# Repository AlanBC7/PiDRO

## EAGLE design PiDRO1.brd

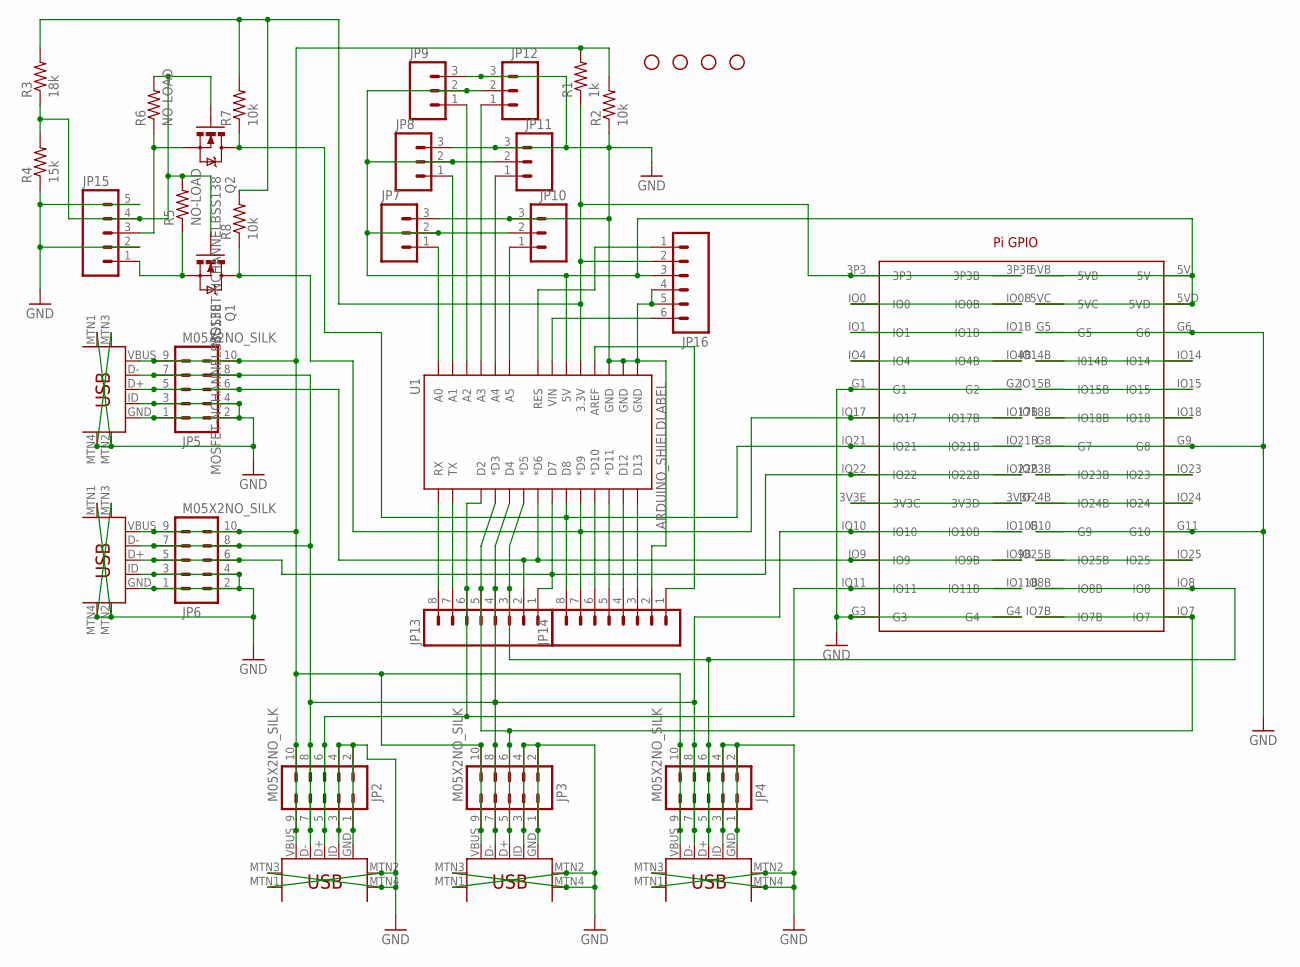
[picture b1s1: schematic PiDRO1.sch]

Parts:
JP2, JP3, JP4, JP5, JP6: M05X2NO_SILK; 2X5_NOSILK
JP7, JP8, JP9, JP10, JP11, JP12: M03LOCK_NO_SILK; 1X03_LOCK_NO_SILK
JP13, JP14: M08; 1X08_PIN1_NO_SILK
JP15: M05PTH; 1X05
JP16: M06LOCK; 1X06_LOCK
Q1, Q2: MOSFET-NCHANNELBSS138; SOT23
R1: 1k; 0805
R2, R7, R8: 10k; 0805
R3: 18k; 0805
R4: 15k; 0805
R5, R6: NO-LOAD; 0805
STANDOFF1, STANDOFF2, STANDOFF3, STANDOFF4: STAND-OFF
U1: ARDUINO_SHIELDLABEL; DUEMILANOVE_SHIELD
U$1: PIGPIO_2X; PI_GPIO_2X
U$2, U$3, U$4, U$5, U$6: USB-MINIB-5PIN; USB-MINIB

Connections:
GND: JP2.1, JP2.2, JP2.3, JP2.4, JP3.1, JP3.2, JP3.3, JP3.4, JP4.1, JP4.2, JP4.3, JP4.4, JP5.1, JP5.2, JP5.3, JP5.4, JP6.1, JP6.2, JP6.3, JP6.4, JP7.3, JP8.3, JP9.3, JP10.3, JP11.3, JP12.3, JP14.2, JP15.2, JP15.5, JP16.4, JP16.5, R2.1, R4.1, U1.GND@0 (GND), U1.GND@1 (GND), U1.GND@2 (GND), U$1.G1, U$1.G2, U$1.G3, U$1.G4, U$1.G5, U$1.G6, U$1.G8 (G7), U$1.G9 (G8), U$1.G10 (G9), U$1.G11 (G10), U$2.GND, U$2.ID, U$2.MTN1 (MTN2), U$2.MTN2 (MTN3), U$2.MTN3 (MTN1), U$2.MTN4, U$3.GND, U$3.ID, U$3.MTN1 (MTN2), U$3.MTN2 (MTN3), U$3.MTN3 (MTN1), U$3.MTN4, U$4.GND, U$4.ID, U$4.MTN1 (MTN2), U$4.MTN2 (MTN3), U$4.MTN3 (MTN1), U$4.MTN4, U$5.GND, U$5.ID, U$5.MTN1 (MTN2), U$5.MTN2 (MTN3), U$5.MTN3 (MTN1), U$5.MTN4, U$6.GND, U$6.ID, U$6.MTN1 (MTN2), U$6.MTN2 (MTN3), U$6.MTN3 (MTN1), U$6.MTN4
unnamed: JP15.4, Q1.1 (G), Q2.1 (G), R3.1, R4.2, R5.2, R6.2
unnamed: JP2.7, JP2.8, JP3.7, JP3.8, JP4.7, JP4.8, JP5.7, JP5.8, JP6.7, JP6.8, JP13.4, U1.D4, U$1.IO10, U$1.IO10B, U$2.D-, U$3.D-, U$4.D-, U$5.D-, U$6.D-
unnamed: JP2.5, JP2.6, JP13.6, U1.D2, U$1.IO11, U$1.IO11B, U$2.D+
unnamed: JP13.8, U1.RX
unnamed: JP15.1, Q1.2 (S), R5.1
unnamed: JP15.3, Q2.2 (S), R6.1
unnamed: JP14.8, Q2.3 (D), R7.1, U1.D8, U$1.IO21, U$1.IO21B
unnamed: JP13.7, U1.TX
unnamed: U$1.IO0, U$1.IO0B
unnamed: JP14.7, Q1.3 (D), R8.1, U1.D9 (*D9), U$1.IO17, U$1.IO17B
unnamed: JP11.1, U1.A4
unnamed: U$1.IO1, U$1.IO1B
unnamed: U$1.IO4, U$1.IO4B
unnamed: U$1.3V3E (3V3C), U$1.3V3F (3V3D)
unnamed: JP3.5, JP3.6, JP13.5, U1.D3 (*D3), U$1.IO7, U$1.IO7B, U$3.D+
unnamed: JP2.9, JP2.10, JP3.9, JP3.10, JP4.9, JP4.10, JP5.9, JP5.10, JP6.9, JP6.10, R1.2, R2.2, U$2.VBUS, U$3.VBUS, U$4.VBUS, U$5.VBUS, U$6.VBUS
unnamed: JP6.5, JP6.6, JP13.1, U1.D7, U$1.IO22, U$1.IO22B, U$6.D+
unnamed: JP4.5, JP4.6, JP13.3, U1.D5 (*D5), U$1.IO8, U$1.IO8B, U$4.D+
unnamed: JP5.5, JP5.6, JP13.2, U1.D6 (*D6), U$1.IO9, U$1.IO9B, U$5.D+
unnamed: JP14.3, U1.D13
unnamed: JP14.4, U1.D12
unnamed: JP14.5, U1.D11 (*D11)
unnamed: JP14.6, U1.D10 (*D10)
unnamed: U$1.IO25, U$1.IO25B
unnamed: JP7.1, U1.A0
unnamed: U$1.IO24, U$1.IO24B
unnamed: JP8.1, U1.A1
unnamed: U$1.IO23, U$1.IO23B
unnamed: JP9.1, U1.A2
unnamed: JP12.1, U1.A3
unnamed: JP10.1, U1.A5
unnamed: JP7.2, JP8.2, JP9.2, JP10.2, JP11.2, JP12.2, JP16.3, U1.5V, U$1.5V, U$1.5VB, U$1.5VC, U$1.5VD
unnamed: JP16.2, R1.1, R3.2, R7.2, R8.2, U1.3.3V, U$1.3P3, U$1.3P3B
unnamed: U$1.IO18, U$1.IO18B
unnamed: JP16.1, U1.RES
unnamed: JP16.6, U1.VIN
unnamed: JP14.1, U1.AREF
unnamed: U$1.IO15, U$1.IO15B
unnamed: U$1.IO14, U$1.IO14B (I014B)

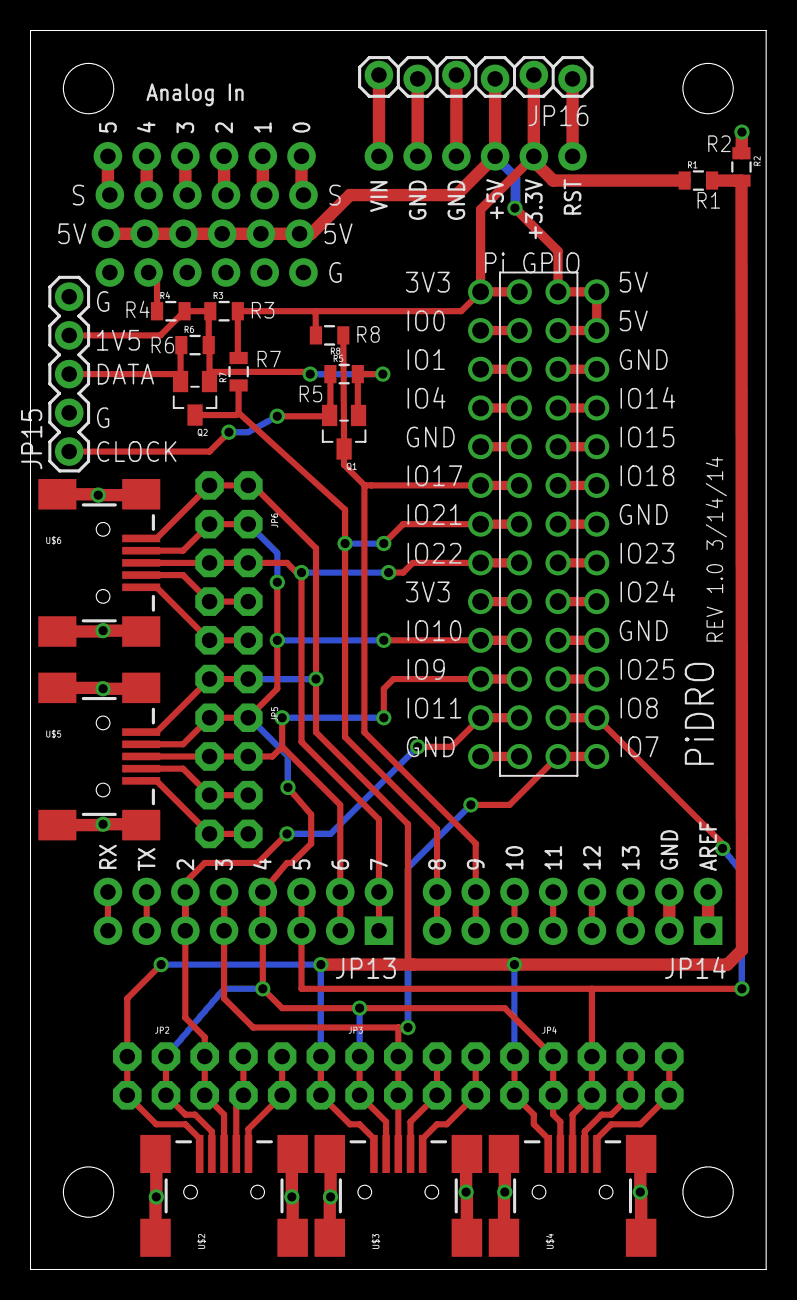
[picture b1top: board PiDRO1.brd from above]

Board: 2 copper layers, 48.3 x 81.3 mm, 36 parts (0 on the bottom side), 40 nets.

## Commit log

2014-07-10 Digital Readout for iGage scales on the Raspberry Pi
    This is the completed first fully working version of PiDRO. This
    project reads digital scales mounted on a milling machine and/or lathe.
    The data is displayed on a large computer screen. Inch or mm display is
    provided along with a variety of ways to zero the scales. The scales
    are inexpensive. This work may aid others in adding scales to their
    projects.
2014-07-10 Doc change
    Added file information

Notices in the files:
parts and their libraries:
SparkFun-Boards: Licensing: CC v3.0 Share-Alike You are welcome to use this library for commercial purposes.
SparkFun-Connectors: Licensing: Creative Commons ShareAlike 4.0 International - https://creativecommons.org/licenses/by-sa/4.0
